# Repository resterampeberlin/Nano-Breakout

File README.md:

# Purpose

# Credits

This open source code project is has been proudfully produced in Berlin (and other places around the globe) by

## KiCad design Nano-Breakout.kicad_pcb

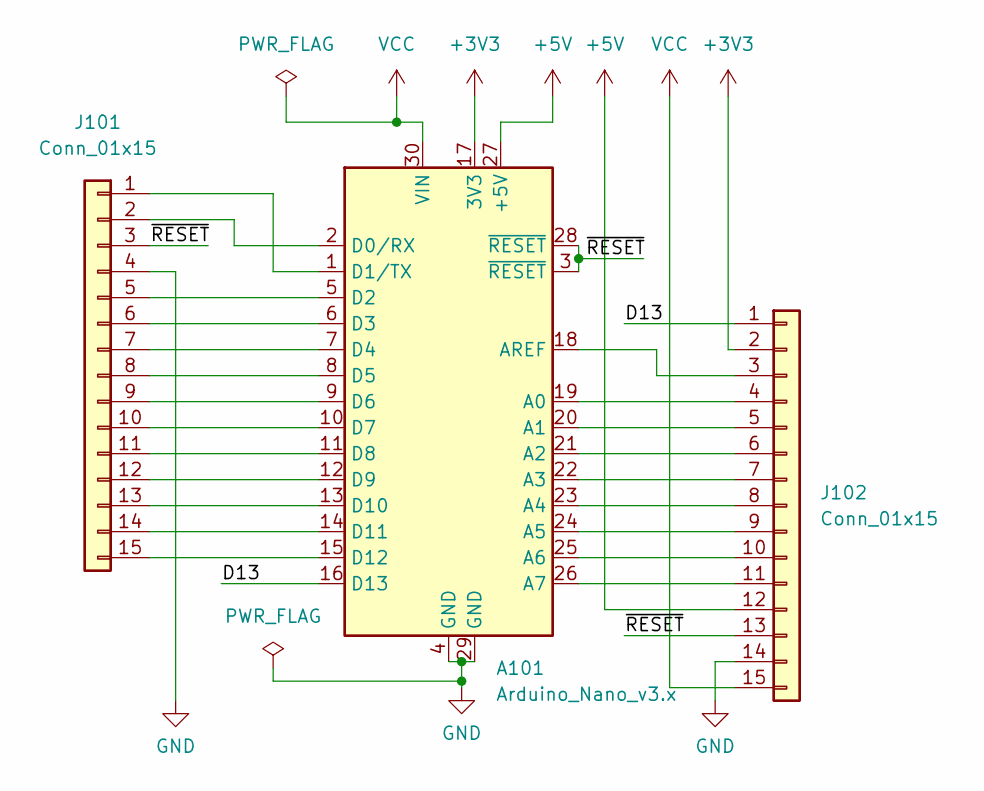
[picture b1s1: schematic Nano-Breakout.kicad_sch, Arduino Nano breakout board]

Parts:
A101: Arduino_Nano_v3.x; Arduino_Nano_Stacking_THT
J101, J102: Conn_01x15; PinHeader_1x15_P2.54mm_Vertical

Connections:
+3V3: A101.17 (3V3), J102.2
+5V: A101.27 (+5V), J102.12
/D13: A101.16 (D13), J102.1
/~RESET: A101.3 (~RESET), A101.28 (~RESET), J101.3, J102.13
GND: A101.4 (GND), A101.29 (GND), J101.4, J102.14
unnamed: A101.1 (D1/TX), J101.1
unnamed: A101.2 (D0/RX), J101.2
unnamed: A101.5 (D2), J101.5
unnamed: A101.6 (D3), J101.6
unnamed: A101.7 (D4), J101.7
unnamed: A101.8 (D5), J101.8
unnamed: A101.9 (D6), J101.9
unnamed: A101.10 (D7), J101.10
unnamed: A101.11 (D8), J101.11
unnamed: A101.12 (D9), J101.12
unnamed: A101.13 (D10), J101.13
unnamed: A101.14 (D11), J101.14
unnamed: A101.15 (D12), J101.15
unnamed: A101.18 (AREF), J102.3
unnamed: A101.19 (A0), J102.4
unnamed: A101.20 (A1), J102.5
unnamed: A101.21 (A2), J102.6
unnamed: A101.22 (A3), J102.7
unnamed: A101.23 (A4), J102.8
unnamed: A101.24 (A5), J102.9
unnamed: A101.25 (A6), J102.10
unnamed: A101.26 (A7), J102.11
VCC: A101.30 (VIN), J102.15

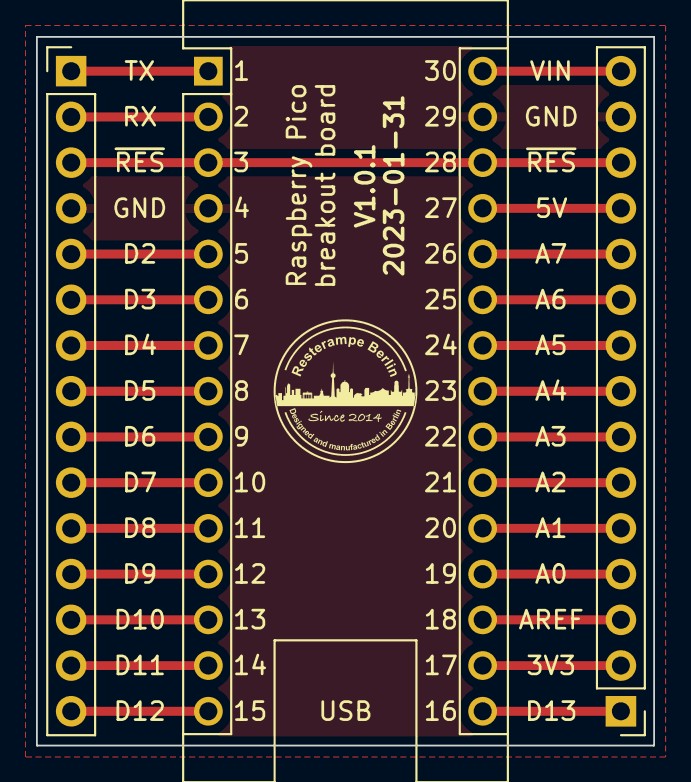
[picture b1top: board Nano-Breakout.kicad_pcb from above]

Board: 2 copper layers, 34.3 x 39.4 mm, 3 parts (0 on the bottom side), 28 nets.

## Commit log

2023-01-30 Initial version
2023-01-31 Production
2023-01-31 Documentation update, name of board on PCB
2023-02-02 Added 3D stacking header
2023-02-02 Names streamlined

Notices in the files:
Nano-Breakout.kicad_pcb:
https://creativecommons.org/licenses/by-nc/4.0
License CC BY-NC 4.0
